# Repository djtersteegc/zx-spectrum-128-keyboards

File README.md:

# zx-spectrum-128-keyboards
Work in progress...

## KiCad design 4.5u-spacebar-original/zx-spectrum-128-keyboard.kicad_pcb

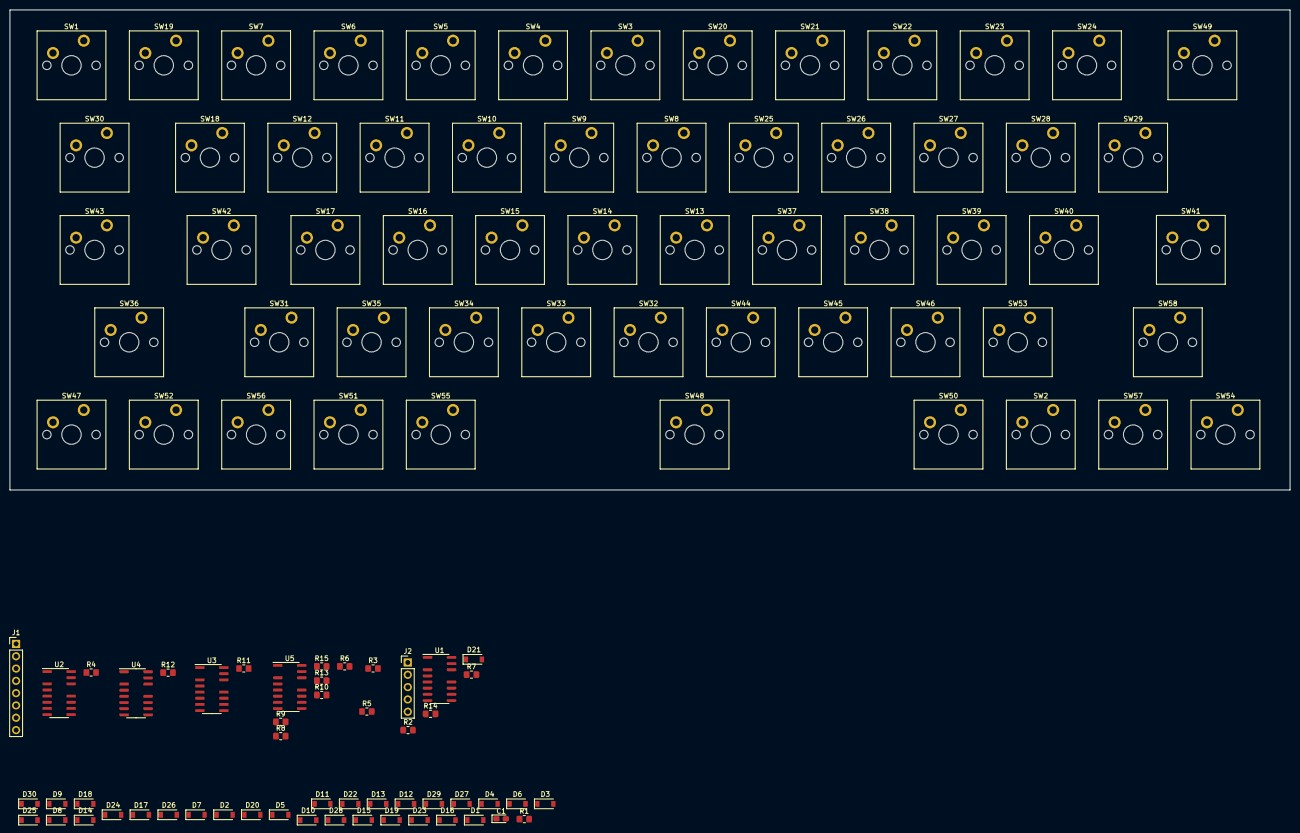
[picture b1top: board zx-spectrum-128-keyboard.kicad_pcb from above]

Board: 2 copper layers, 264.2 x 99.1 mm, 111 parts (0 on the bottom side), 33 nets, no tracks yet.

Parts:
C1: C_Polarized_Small; CP_EIA-2012-12_Kemet-R_Pad1.30x1.05mm_HandSolder
D1, D2, D3, D4, D5, D6, D7, D8, D9, D10, D11, D12, D13, D14, D15, D16, D17, D18, D19, D20, D21, D22, D23, D24, D25, D26, D27, D28, D29, D30: BAT42W-V; D_SOD-123
J1: KB2; PinHeader_1x08_P2.54mm_Vertical
J2: KB1; PinHeader_1x05_P2.54mm_Vertical
R1, R2, R3, R4, R5, R6, R7, R8, R9, R10, R11, R12, R13, R14, R15: 10K; R_0805_2012Metric_Pad1.20x1.40mm_HandSolder
SW1: INV VIDEO; SW_Cherry_MX_PCB_1.00u
SW2: DOWN; SW_Cherry_MX_PCB_1.00u
SW3: 5; SW_Cherry_MX_PCB_1.00u
SW4: 4; SW_Cherry_MX_PCB_1.00u
SW5: 3; SW_Cherry_MX_PCB_1.00u
SW6: 2; SW_Cherry_MX_PCB_1.00u
SW7: 1; SW_Cherry_MX_PCB_1.00u
SW8: T; SW_Cherry_MX_PCB_1.00u
SW9: R; SW_Cherry_MX_PCB_1.00u
SW10: E; SW_Cherry_MX_PCB_1.00u
SW11: W; SW_Cherry_MX_PCB_1.00u
SW12: Q; SW_Cherry_MX_PCB_1.00u
SW13: G; SW_Cherry_MX_PCB_1.00u
SW14: F; SW_Cherry_MX_PCB_1.00u
SW15: D; SW_Cherry_MX_PCB_1.00u
SW16: S; SW_Cherry_MX_PCB_1.00u
SW17: A; SW_Cherry_MX_PCB_1.00u
SW18: GRAPH; SW_Cherry_MX_PCB_1.00u
SW19: TRUE VIDEO; SW_Cherry_MX_PCB_1.00u
SW20: 6; SW_Cherry_MX_PCB_1.00u
SW21: 7; SW_Cherry_MX_PCB_1.00u
SW22: 8; SW_Cherry_MX_PCB_1.00u
SW23: 9; SW_Cherry_MX_PCB_1.00u
SW24: 0; SW_Cherry_MX_PCB_1.00u
SW25: Y; SW_Cherry_MX_PCB_1.00u
SW26: U; SW_Cherry_MX_PCB_1.00u
SW27: I; SW_Cherry_MX_PCB_1.00u
SW28: O; SW_Cherry_MX_PCB_1.00u
SW29: P; SW_Cherry_MX_PCB_1.00u
SW30: DELETE; SW_Cherry_MX_PCB_1.50u
SW31: CAPS LOCK; SW_Cherry_MX_PCB_1.00u
SW32: V; SW_Cherry_MX_PCB_1.00u
SW33: C; SW_Cherry_MX_PCB_1.00u
SW34: X; SW_Cherry_MX_PCB_1.00u
SW35: Z; SW_Cherry_MX_PCB_1.00u
SW36, SW58: CAPS SHIFT; SW_Cherry_MX_PCB_2.25u
SW37: H; SW_Cherry_MX_PCB_1.00u
SW38: J; SW_Cherry_MX_PCB_1.00u
SW39: K; SW_Cherry_MX_PCB_1.00u
SW40: L; SW_Cherry_MX_PCB_1.00u
SW41: ENTER; SW_Cherry_MX_PCB_1.75u
SW42: EDIT; SW_Cherry_MX_PCB_1.25u
SW43: EXT MODE; SW_Cherry_MX_PCB_1.50u
SW44: B; SW_Cherry_MX_PCB_1.00u
SW45: N; SW_Cherry_MX_PCB_1.00u
SW46: M; SW_Cherry_MX_PCB_1.00u
SW47, SW54: SYMB SHIFT; SW_Cherry_MX_PCB_1.00u
SW48: SPACE; SW_Cherry_MX_PCB_4.50u
SW49: BREAK; SW_Cherry_MX_PCB_1.50u
SW50: UP; SW_Cherry_MX_PCB_1.00u
SW51: LEFT; SW_Cherry_MX_PCB_1.00u
SW52: SEMI COLON; SW_Cherry_MX_PCB_1.00u
SW53: PERIOD; SW_Cherry_MX_PCB_1.00u
SW55: RIGHT; SW_Cherry_MX_PCB_1.00u
SW56: QUOTES; SW_Cherry_MX_PCB_1.00u
SW57: COMMA; SW_Cherry_MX_PCB_1.00u
U1, U2, U3, U4, U5: 4066; SOIC-14-16_3.9x9.9mm_P1.27mm

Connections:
+5V: C1.1, D18.1 (K), D19.1 (K), D20.1 (K), D21.1 (K), D22.1 (K), SW1.1, SW2.1, SW18.1, SW19.1, SW30.1, SW31.1, SW42.1, SW43.1, SW49.1, SW50.1, SW51.1, SW52.1, SW53.1, SW55.1, SW56.1, SW57.1, U1.14 (VDD), U2.14 (VDD), U3.14 (VDD), U4.14 (VDD), U5.14 (VDD)
/BREAK-1: D22.2 (A), J2.1, SW7.2, SW12.2, SW17.2, SW24.2, SW29.2, SW36.2, SW41.2, SW48.2, SW58.1, U2.3, U2.10, U3.9
/CAPS LOCK-1: D21.2 (A), J2.2, SW6.2, SW11.2, SW16.2, SW23.2, SW54.1, U1.9, U4.10, U5.10
/CAPS LOCK-2: D1.1 (K), J1.1, SW3.1, SW4.1, SW5.1, SW6.1, SW7.1, U1.1, U1.3, U1.8, U2.11, U4.4
/CAPS SHIFT ON: D2.1 (K), D3.1 (K), D6.1 (K), D7.1 (K), D10.1 (K), D11.1 (K), D14.1 (K), D15.1 (K), D23.1 (K), D24.1 (K), D25.1 (K), D28.1 (K)
/CAPS SHIFT-2: D12.1 (K), J1.6, SW32.1, SW33.1, SW34.1, SW35.1, SW36.1, SW58.2, U4.1
/COMMA-2: D16.1 (K), J1.8, SW44.1, SW45.1, SW46.1, SW47.1, SW48.1, SW54.2, U3.8, U4.11, U5.4, U5.8
/DELETE-2: D8.1 (K), J1.4, SW20.1, SW21.1, SW22.1, SW23.1, SW24.1, U1.11, U2.1, U2.4, U3.1, U4.8
/DOWN-1: D18.2 (A), J2.5, SW3.2, U1.10, U4.3
/INV VIDEO-1: D19.2 (A), J2.4, SW4.2, U5.9
/PERIOD-1: D20.2 (A), J2.3, SW5.2, U1.4, U4.9, U5.3
/QUOTES-2: D9.1 (K), J1.5, SW25.1, SW26.1, SW27.1, SW28.1, SW29.1, U5.1, U5.11
/SYMB SHIFT ON: D17.1 (K), D26.1 (K), D27.1 (K), D29.1 (K), D30.1 (K), U4.12
GND: C1.2, D1.2 (A), D4.2 (A), D5.2 (A), D8.2 (A), D9.2 (A), D12.2 (A), D13.2 (A), D16.2 (A), R1.2, R2.2, R3.2, R4.2, R5.2, R6.2, R7.2, R8.2, R9.2, R10.2, R11.2, R12.2, R13.2, R14.2, R15.2, U1.7 (VSS), U2.7 (VSS), U3.7 (VSS), U4.7 (VSS), U5.7 (VSS)
unnamed: D2.2 (A), R1.1, SW1.2
unnamed: D3.2 (A), R2.1, SW2.2, U1.12
unnamed: D4.1 (K), J1.2, SW8.1, SW9.1, SW10.1, SW11.1, SW12.1
unnamed: D5.1 (K), J1.3, SW13.1, SW14.1, SW15.1, SW16.1, SW17.1
unnamed: D6.2 (A), R3.1, SW18.2
unnamed: D7.2 (A), R4.1, SW19.2, U1.5
unnamed: D10.2 (A), R5.1, SW30.2, U2.5
unnamed: D11.2 (A), R6.1, SW31.2, U1.6
unnamed: D13.1 (K), J1.7, SW37.1, SW38.1, SW39.1, SW40.1, SW41.1
unnamed: D14.2 (A), R7.1, SW42.2, U2.12
unnamed: D15.2 (A), D17.2 (A), SW43.2
unnamed: D23.2 (A), R8.1, SW49.2, U3.6
unnamed: D24.2 (A), R9.1, SW50.2
unnamed: D25.2 (A), R10.1, SW51.2, U4.5
unnamed: D26.2 (A), R11.1, SW52.2, U5.12
unnamed: D27.2 (A), R12.1, SW53.2, U5.5
unnamed: D28.2 (A), R13.1, SW55.2, U4.6
unnamed: D29.2 (A), R14.1, SW56.2
unnamed: D30.2 (A), R15.1, SW57.2, U5.6

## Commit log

2023-02-11 NOT COMPLETE!
